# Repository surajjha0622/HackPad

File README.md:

# HackPad

A compact 6-key programmable macropad built using the **Seeed Studio XIAO RP2040**.

HackPad started as a project to learn the complete hardware design workflow—from schematic capture and PCB design to enclosure design and firmware development. Instead of using an existing macropad, I wanted to build one from scratch and understand every part of the process.

The project combines mechanical switches, a rotary encoder, and a small OLED display into a compact device that can be customized for productivity, media control, programming shortcuts, CAD software, or everyday workflows.

---

## Features

- 6 Mechanical Keys
- Rotary Encoder with Push Button
- 0.91" SSD1306 OLED Display
- USB Type-C Connectivity
- Powered by Seeed Studio XIAO RP2040
- Custom PCB designed in KiCad
- 3D Printed Enclosure
- QMK Firmware 

---

## PCB

---

## Schematic

---

## 3D PCB Render

---

## Enclosure Design

| Front | Edge |
|:------:|:----:|
|  |  |

---

## Tech Stack

- KiCad 9
- Seeed Studio XIAO RP2040
- QMK Firmware *(In Progress)*
- 3D Printing
- Git & GitHub

---

## Current Status

- ✅ Schematic Complete
- ✅ PCB Designed
- ✅ 3D PCB Verified
- ✅ Enclosure Designed
- ✅ Gerber Files Generated
- 🔄 Firmware Development
- ⏳ PCB Manufacturing
- ⏳ Assembly & Testing

---

## What I Learned

This project helped me gain hands-on experience with:

- PCB Design
- Schematic Design
- Component Selection
- PCB Routing
- 3D Enclosure Design
- Hardware Documentation
- GitHub Project Organization

---

## 🤝 Feedback

This project is still evolving, and I'd love to hear suggestions or ideas for improvements. If you spot something that could be done better, feel free to open an issue or reach out!

Thanks for checking out HackPad! 🚀

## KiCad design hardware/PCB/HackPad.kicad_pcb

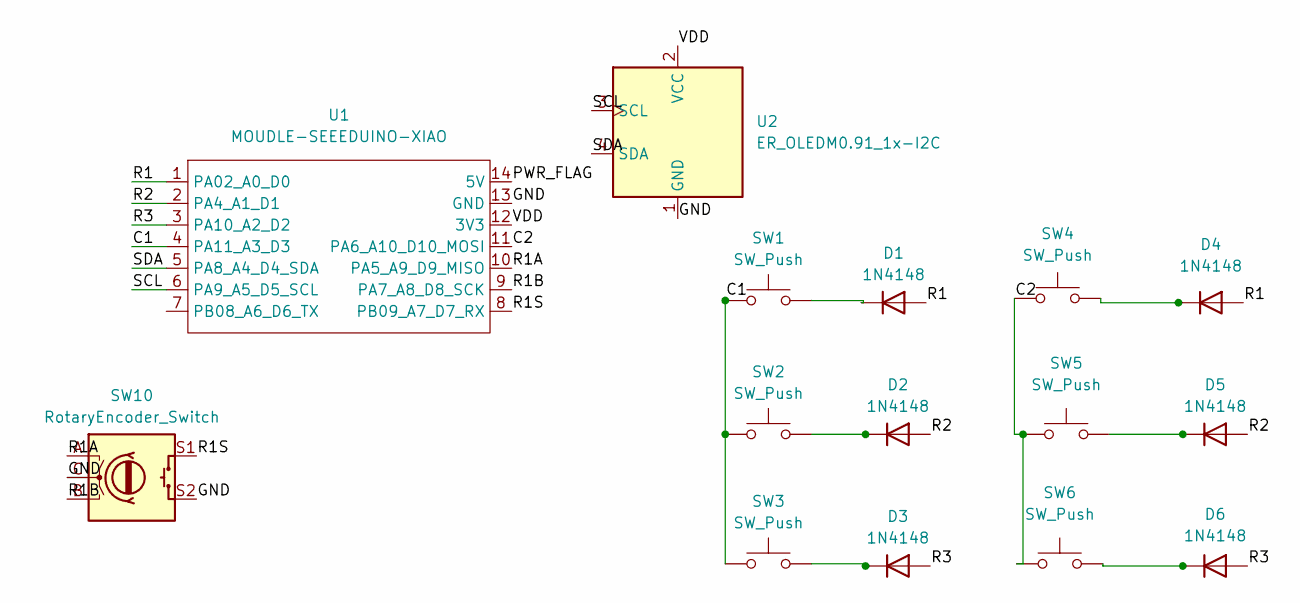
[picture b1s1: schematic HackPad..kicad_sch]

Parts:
D1, D2, D3, D4, D5, D6: 1N4148; D_DO-35_SOD27_P7.62mm_Horizontal
SW1, SW2, SW3, SW4, SW5, SW6: SW_Push; SW_Cherry_MX_1.00u_PCB
SW10: RotaryEncoder_Switch; RotaryEncoder_Alps_EC11E-Switch_Vertical_H20mm
U1: MOUDLE-SEEEDUINO-XIAO; XIAO-Generic-Hybrid-14P-2.54-21X17.8MM
U2: ER_OLEDM0.91_1x-I2C

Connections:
/C1: SW1.1, SW2.1, SW3.1, U1.4 (PA11_A3_D3)
/C2: SW4.1, SW5.1, SW6.1, U1.11 (PA6_A10_D10_MOSI)
/GND: SW10.C, SW10.S2, U1.13 (GND), U2.1 (GND)
/PWR_FLAG: U1.14 (5V)
/R1: D1.2 (A), D4.2 (A), U1.1 (PA02_A0_D0)
/R1A: SW10.A, U1.10 (PA5_A9_D9_MISO)
/R1B: SW10.B, U1.9 (PA7_A8_D8_SCK)
/R1S: SW10.S1, U1.8 (PB09_A7_D7_RX)
/R2: D2.2 (A), D5.2 (A), U1.2 (PA4_A1_D1)
/R3: D3.2 (A), D6.2 (A), U1.3 (PA10_A2_D2)
/SCL: U1.6 (PA9_A5_D5_SCL), U2.3 (SCL)
/SDA: U1.5 (PA8_A4_D4_SDA), U2.4 (SDA)
/VDD: U1.12 (3V3), U2.2 (VCC)
unnamed: D1.1 (K), SW1.2
unnamed: D2.1 (K), SW2.2
unnamed: D3.1 (K), SW3.2
unnamed: D4.1 (K), SW4.2
unnamed: D5.1 (K), SW5.2
unnamed: D6.1 (K), SW6.2

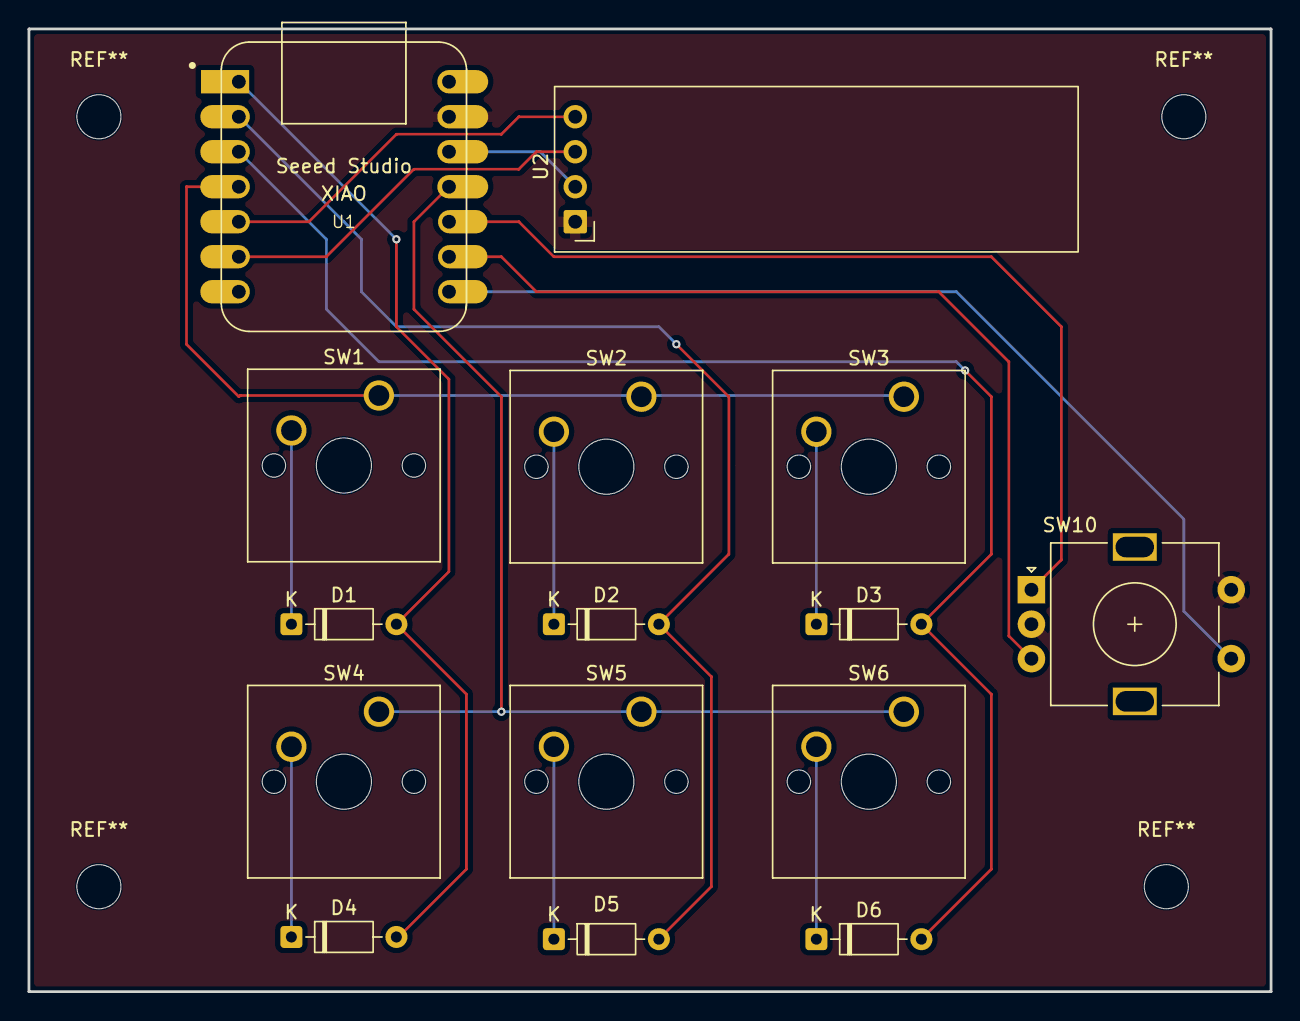
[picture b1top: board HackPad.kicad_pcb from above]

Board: 2 copper layers, 90.2 x 69.9 mm, 15 parts (0 on the bottom side), 18 nets.

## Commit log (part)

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2026-06-12 Add initial README for HACKPAD project
2026-06-12 Correct capitalization in README description
